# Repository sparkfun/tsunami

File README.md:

_Note: This repository is for the Tsunami Super WAV Trigger v1.1. For v1.2, check out the [Tsunami Super WAV Trigger (Qwiic) v1.2 GitHub repository](https://github.com/sparkfun/SparkFun_Tsunami_Super_WAV_Trigger_Qwiic)._

Tsunami Super WAV Trigger
========================================

[*Tsunami Super WAV Trigger (WIG-13810)*](https://www.sparkfun.com/products/retired/13810)

Tsunami is a polyphonic Wav file player with 4 stereo (or 8 mono) outputs.  Wav files can be triggered using the 16 onboard contacts, via MIDI, or using a serial connection to a PC or other microcontroller.

Repository Contents
-------------------

* **/Documentation** - Data sheets, additional product information
* **/Hardware** - Eagle design files (.brd, .sch)
* **/Production** - Production panel files (.brd)

Documentation
--------------
* **[Hookup Guide](https://learn.sparkfun.com/tutorials/tsunami-hookup-guide)** - Basic hookup guide for Tsunami v1.1.
* **[Official User Guide](https://cdn.sparkfun.com/assets/e/9/9/8/e/Tsunami_UserGuide_20230114.pdf)** - More detailed user guide, hosted by Robertsonics.
* **[Official Downloads Page](http://robertsonics.com/downloads/)** - Download supporting files, including firmware updates and the configuration utility.
* **[SparkFun Fritzing repo](https://github.com/sparkfun/Fritzing_Parts)** - Fritzing diagrams for SparkFun products.
* **[SparkFun 3D Model repo](https://github.com/sparkfun/3D_Models)** - 3D models of SparkFun products.

Product Versions
----------------
* [WIG-13810](https://www.sparkfun.com/products/13810) - First hardware revision.

Version History
---------------
* [Initial production Release](https://github.com/sparkfun/tsunami/commit/f42b14d72773535e83374cde73f2ca3f25164abb) - V11 hardware revision.

License Information
-------------------

The hardware design of Tsunami is _**open source**_!

Please review the LICENSE.md file for license information.

If you have any questions or concerns on licensing, please contact techsupport@sparkfun.com.

Distributed as-is; no warranty is given.

- Your friends at SparkFun.

Authors
----

Jamie Robertson @ Robertsonics & Byron Jacquot @ SparkFun Electronics

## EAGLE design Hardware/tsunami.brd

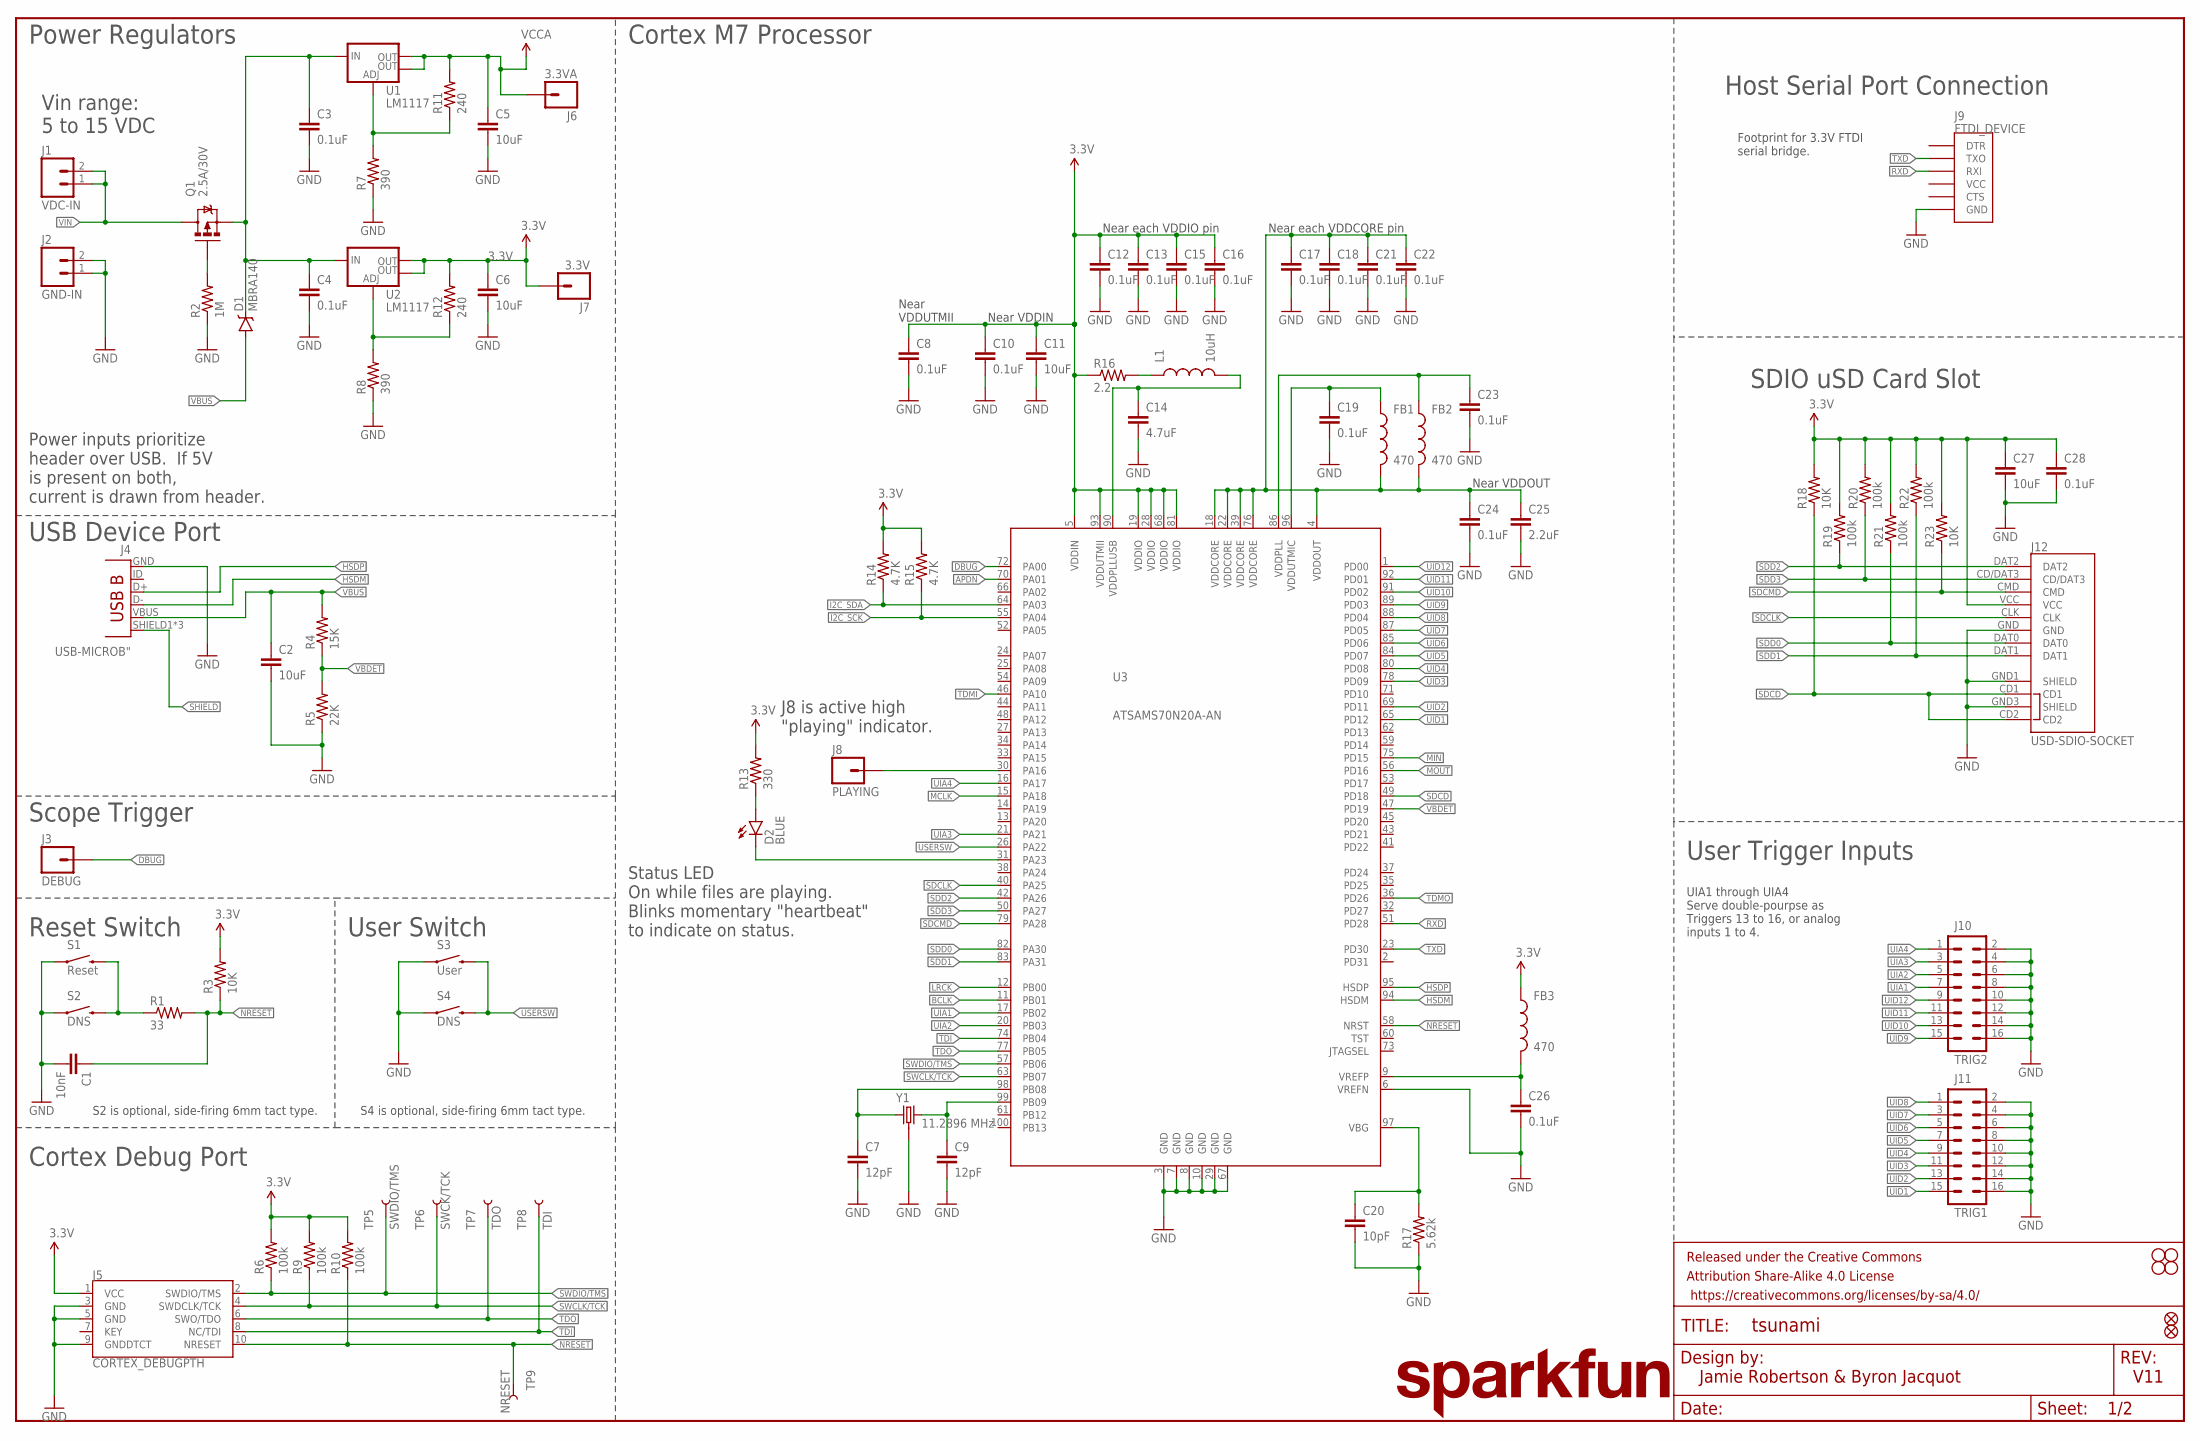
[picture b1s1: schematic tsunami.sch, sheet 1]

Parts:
C1: 10nF; 0603-CAP
C2, C5, C6, C11, C27: 10uF; 0603-CAP
C3, C4, C8, C10, C12, C13, C15, C16, C17, C18, C19, C21, C22, C23, C24, C26, C28: 0.1uF; 0603-CAP
C7, C9: 12pF; 0603-CAP
C14: 4.7uF; 0603-CAP
C20: 10pF; 0603-CAP
C25: 2.2uF; 0603-CAP
D1: MBRA140; SMA-DIODE
D2: BLUE; LED-0603
FB1, FB2, FB3: 470; 0603
FD1, FD2: FIDUCIALUFIDUCIAL; MICRO-FIDUCIAL
FRAME1: FRAME-LEDGER; CREATIVE_COMMONS
H1, H2, H3, H4: STAND-OFF
J1: VDC-IN; 1X02
J2: GND-IN; 1X02
J3: DEBUG; 1X01_NO_SILK
J4: USB-MICROB"; USB-B-MICRO-SMD_V03
J5: CORTEX_DEBUGPTH; 2X5-PTH-1.27MM
J6: 3.3VA; 1X01_NO_SILK
J7: 3.3V; 1X01_NO_SILK
J8: PLAYING; 1X01_NO_SILK
J9: FTDI_DEVICE; FTDI_DEVICE_SIDE
J10: TRIG2; 2X8
J11: TRIG1; 2X8
J12: USD-SDIO-SOCKET; MICRO-SD-SOCKET-SDIO
L1: 10uH; 0805
LOGO1: SFE_LOGO_NAME.2_INCH; SFE_LOGO_NAME_.2
Q1: 2.5A/30V; SOT23-3
R1: 33; 0603-RES
R2: 1M; 0603-RES
R3, R18, R23: 10K; 0603-RES
R4: 15K; 0603-RES
R5: 22K; 0603-RES
R6, R9, R10, R19, R20, R21, R22: 100k; 0603-RES
R7, R8: 390; 0603-RES
R11, R12: 240; 0603-RES
R13: 330; 0603-RES
R14, R15: 4.7K; 0603-RES
R16: 2.2; 0603-RES
R17: 5.62k; 0603-RES
S1: Reset; TACTILE-SWITCH-SMD
S2, S4: DNS; TACTILE-PTH-SIDEEZ
S3: User; TACTILE-SWITCH-SMD
TP5: SWDIO/TMS; TP_15TH
TP6: SWCK/TCK; TP_15TH
TP7: TDO; TP_15TH
TP8: TDI; TP_15TH
TP9: NRESET; TP_15TH
U1, U2: LM1117; SOT223
U3: ATSAMS70N20A-AN; LQFP100
Y1: 11.2896 MHz; CRYSTAL-OSC-SMD-5X3

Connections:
3.3V: C6.1, C8.1, C10.1, C11.1, C12.1, C13.1, C15.1, C16.1, C27.1, C28.1, FB3.1, J5.1 (VCC), J7.1, J12.VCC, R3.2, R6.2, R9.2, R10.2, R12.2, R13.2, R14.2, R15.2, R16.1, R18.2, R19.2, R20.2, R21.2, R22.2, R23.2, U2.2 (OUT), U2.4 (OUT), U3.5 (VDDIN), U3.19 (VDDIO), U3.28 (VDDIO), U3.68 (VDDIO), U3.81 (VDDIO), U3.93 (VDDUTMII); also elsewhere on the board
APDN: U3.70 (PA01); also elsewhere on the board
BCLK: U3.11 (PB01); also elsewhere on the board
DBUG: J3.1, U3.72 (PA00)
GND: C1.2, C2.2, C3.2, C4.2, C5.2, C6.2, C7.2, C8.2, C9.2, C10.2, C11.2, C12.2, C13.2, C14.2, C15.2, C16.2, C17.2, C18.2, C19.2, C20.2, C21.2, C22.2, C23.2, C24.2, C25.2, C26.2, C27.2, C28.2, J2.1, J2.2, J4.GND, J5.3 (GND), J5.5 (GND), J5.9 (GNDDTCT), J9.P$6 (GND), J10.2, J10.4, J10.6, J10.8, J10.10, J10.12, J10.14, J10.16, J11.2, J11.4, J11.6, J11.8, J11.10, J11.12, J11.14, J11.16, J12.GND, J12.GND1 (SHIELD), J12.GND3 (SHIELD), R2.1, R5.1, R7.1, R8.1, R17.1, S1.1, S2.1, S3.1, S4.1, U3.3 (GND), U3.6 (VREFN), U3.7 (GND), U3.8 (GND), U3.10 (GND), U3.29 (GND), U3.67 (GND), Y1.2 (3), Y1.4 (3); also elsewhere on the board
HSDM: J4.D-, U3.94 (HSDM)
HSDP: J4.D+, U3.95 (HSDP)
I2C_SCK: R15.1, U3.55 (PA04); also elsewhere on the board
I2C_SDA: R14.1, U3.64 (PA03); also elsewhere on the board
LRCK: U3.12 (PB00); also elsewhere on the board
MCLK: U3.15 (PA18); also elsewhere on the board
MIN: U3.75 (PD15); also elsewhere on the board
MOUT: U3.56 (PD16); also elsewhere on the board
unnamed: C7.1, U3.98 (PB08), Y1.1
unnamed: C9.1, U3.99 (PB09), Y1.3 (2)
unnamed: C19.1, FB1.1, U3.96 (VDDUTMIC)
unnamed: C14.1, L1.2, U3.90 (VDDPLLUSB)
unnamed: C23.1, FB2.1, U3.86 (VDDPLL)
unnamed: J8.1, U3.30 (PA16)
unnamed: D2.C, U3.31 (PA23)
unnamed: D2.A, R13.1
unnamed: C20.1, R17.2, U3.97 (VBG)
unnamed: C26.1, FB3.2, U3.9 (VREFP)
unnamed: L1.1, R16.2
unnamed: R7.2, R11.1, U1.1 (ADJ)
unnamed: R1.1, S1.3 (2), S2.2
unnamed: R8.2, R12.1, U2.1 (ADJ)
unnamed: Q1.1 (G), R2.2
NRESET: C1.1, J5.10 (NRESET), R1.2, R3.1, R10.1, TP9.P$1, U3.58 (NRST)
REGINPUTS: C3.1, C4.1, D1.C, Q1.2 (S), U1.3 (IN), U2.3 (IN)
RXD: J9.P$3 (RXI), U3.51 (PD28)
SDCD: J12.CD1, J12.CD2, R18.1, U3.49 (PD18)
SDCLK: J12.CLK, U3.40 (PA25)
SDCMD: J12.CMD, R23.1, U3.79 (PA28)
SDD0: J12.DAT0, R21.1, U3.82 (PA30)
SDD1: J12.DAT1, R22.1, U3.83 (PA31)
SDD2: J12.DAT2, R19.1, U3.42 (PA26)
SDD3: J12.CD/DAT3, R20.1, U3.50 (PA27)
SHIELD: J4.SHIELD1 (SHIELD), J4.SHIELD2 (SHIELD), J4.SHIELD3 (SHIELD)
SWCLK/TCK: J5.4 (SWDCLK/TCK), R9.1, TP6.P$1, U3.63 (PB07)
SWDIO/TMS: J5.2 (SWDIO/TMS), R6.1, TP5.P$1, U3.57 (PB06)
TDI: J5.8 (NC/TDI), TP8.P$1, U3.74 (PB04)
TDMI: U3.46 (PA10); also elsewhere on the board
TDMO: U3.36 (PD26); also elsewhere on the board
TDO: J5.6 (SWO/TDO), TP7.P$1, U3.77 (PB05)
TXD: J9.P$2 (TXO), U3.23 (PD30)
UIA1: J10.7, U3.17 (PB02)
UIA2: J10.5, U3.20 (PB03)
UIA3: J10.3, U3.21 (PA21)
UIA4: J10.1, U3.16 (PA17)
UID1: J11.15, U3.65 (PD12)
UID2: J11.13, U3.69 (PD11)
UID3: J11.11, U3.78 (PD09)
UID4: J11.9, U3.80 (PD08)
UID5: J11.7, U3.84 (PD07)
UID6: J11.5, U3.85 (PD06)
UID7: J11.3, U3.87 (PD05)
UID8: J11.1, U3.88 (PD04)
UID9: J10.15, U3.89 (PD03)
UID10: J10.13, U3.91 (PD02)
UID11: J10.11, U3.92 (PD01)
UID12: J10.9, U3.1 (PD00)
USERSW: S3.3 (2), S4.2, U3.26 (PA22)
VBDET: R4.1, R5.2, U3.47 (PD19)
VBUS: C2.1, D1.A, J4.VBUS, R4.2
VCCA: C5.1, J6.1, R11.2, U1.2 (OUT), U1.4 (OUT); also elsewhere on the board
VDDOUT: C17.1, C18.1, C21.1, C22.1, C24.1, C25.1, FB1.2, FB2.2, U3.4 (VDDOUT), U3.18 (VDDCORE), U3.22 (VDDCORE), U3.39 (VDDCORE), U3.76 (VDDCORE)
VIN: J1.1, J1.2, Q1.3 (D)

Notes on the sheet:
Jamie Robertson & Byron Jacquot
V11
Near each VDDCORE pin
Near each VDDIO pin
Near VDDUTMII
Near VDDIN
Near VDDOUT
Power Regulators
USB Device Port
Scope Trigger
Cortex Debug Port
Cortex M7 Processor
SDIO uSD Card Slot
User Trigger Inputs
Reset Switch
S2 is optional, side-firing 6mm tact type.
Vin range: 5 to 15 VDC
Status LED On while files are playing. Blinks momentary "heartbeat" to indicate on status.
Power inputs prioritize header over USB. If 5V is present on both, current is drawn from header.
UIA1 through UIA4 Serve double-pourpse as Triggers 13 to 16, or analog inputs 1 to 4.
Host Serial Port Connection
Footprint for 3.3V FTDI serial bridge.
User Switch
J8 is active high "playing" indicator.
S4 is optional, side-firing 6mm tact type.

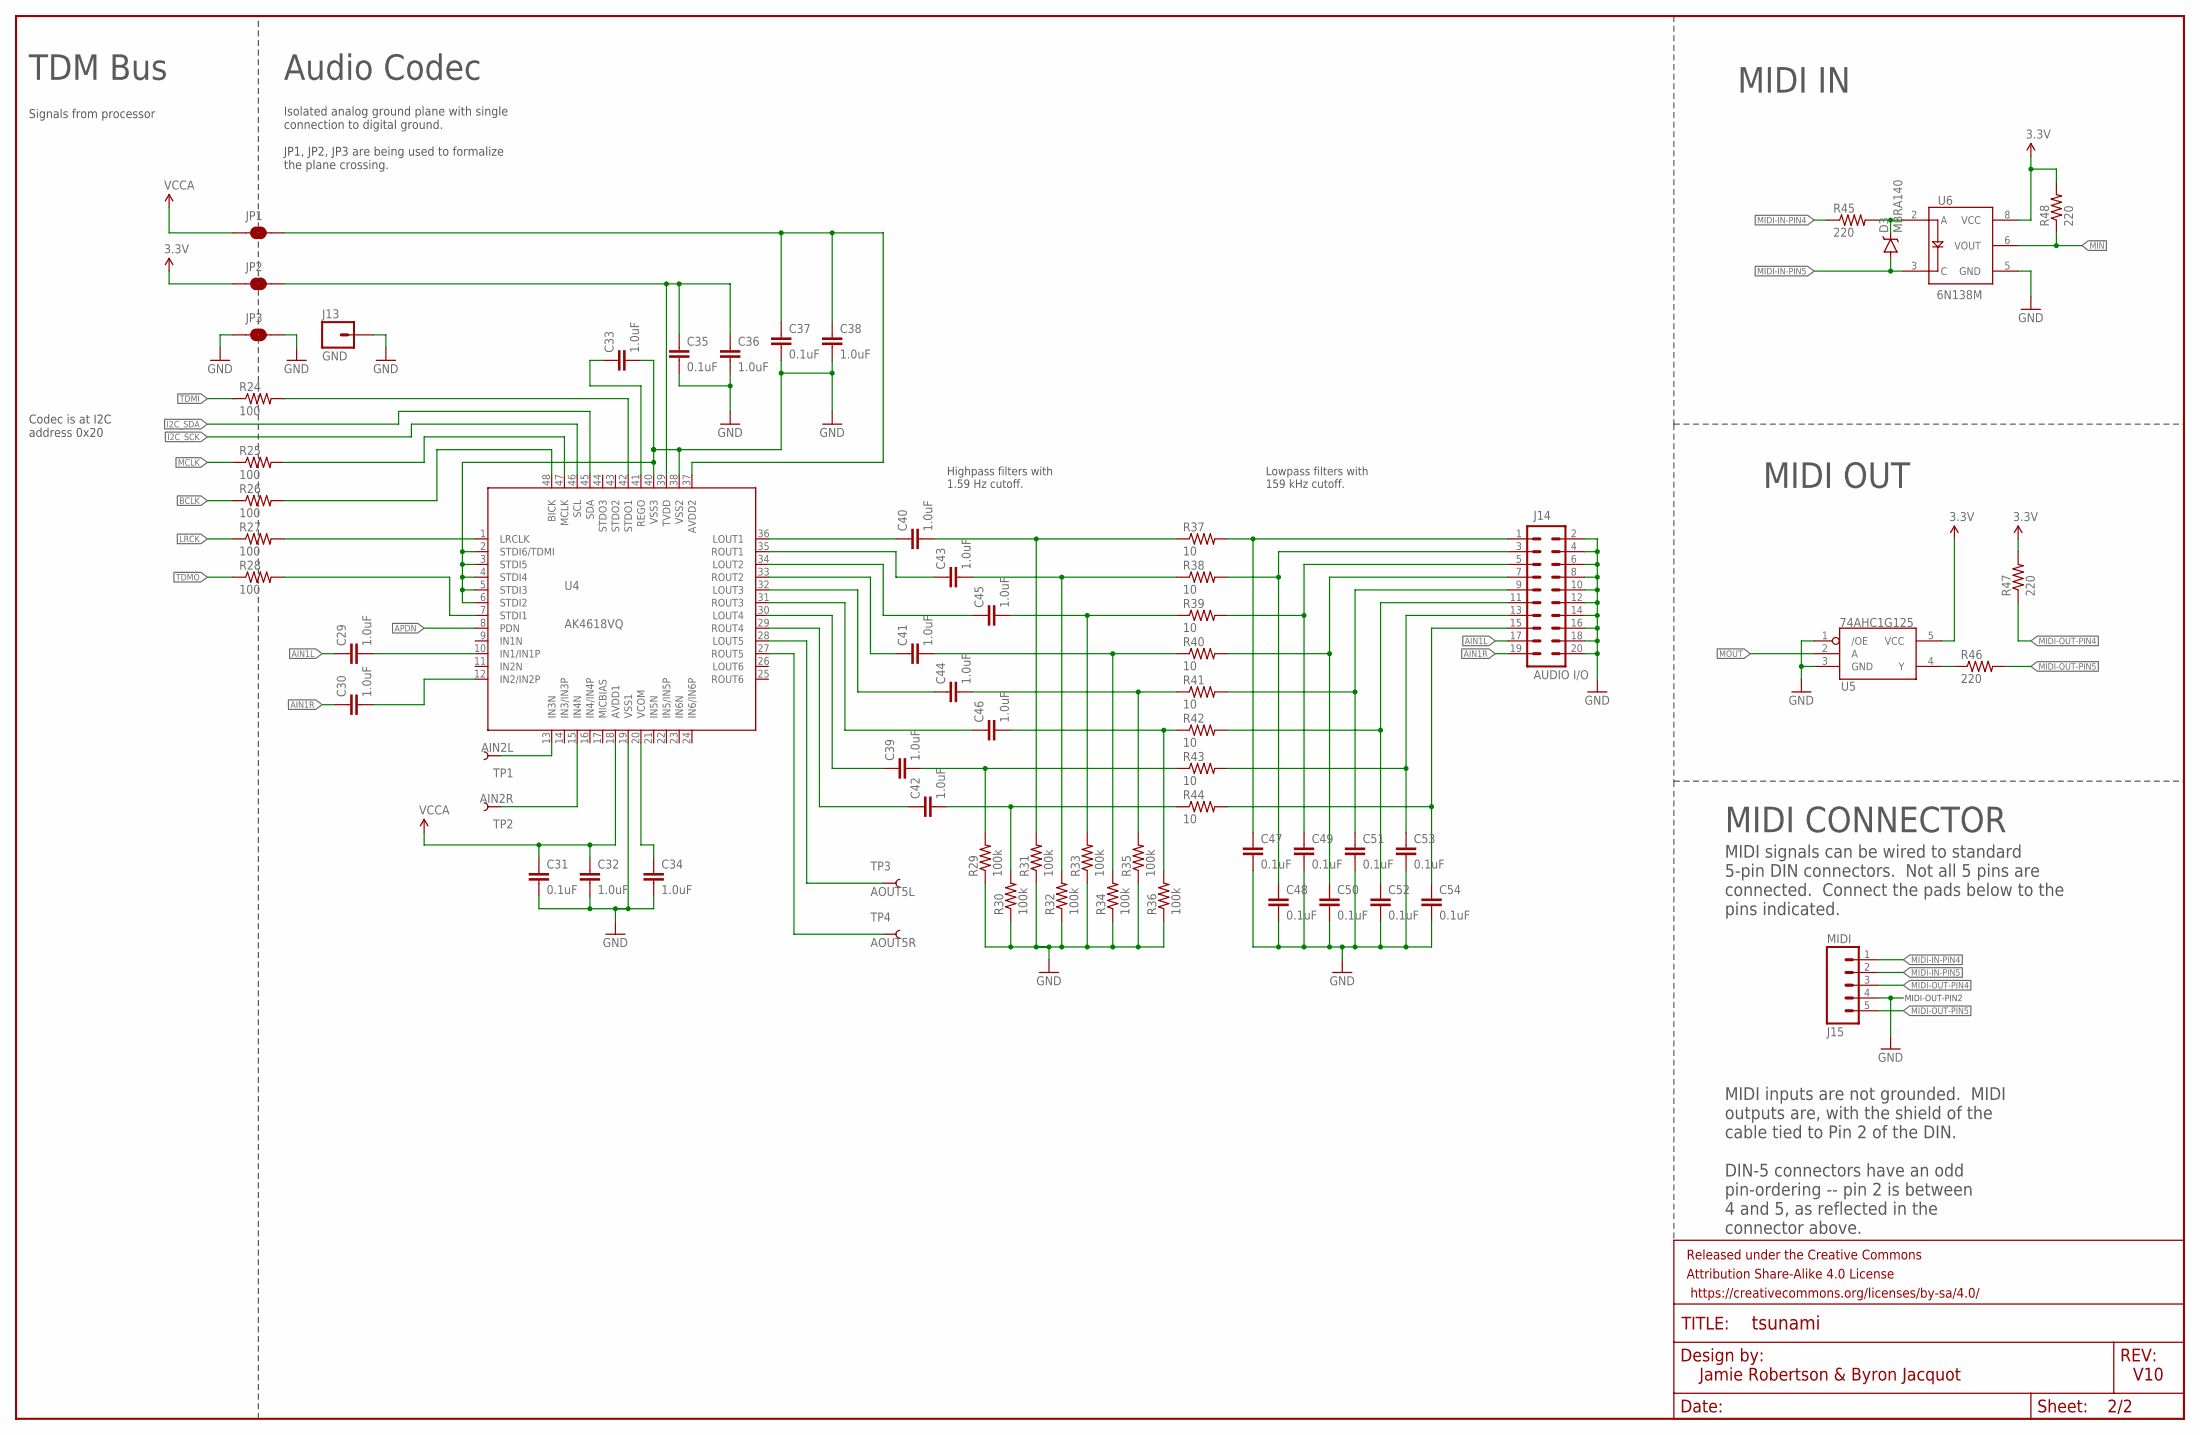
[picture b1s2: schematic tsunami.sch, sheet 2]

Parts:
C29, C30, C32, C33, C34, C36, C38, C39, C40, C41, C42, C43, C44, C45, C46: 1.0uF; 0603-CAP
C31, C35, C37, C47, C48, C49, C50, C51, C52, C53, C54: 0.1uF; 0603-CAP
D3: MBRA140; SMA-DIODE
FRAME2: FRAME-LEDGER; CREATIVE_COMMONS
J13: GND; 1X01_NO_SILK
J14: AUDIO I/O; 2X10
J15: MIDI; 1X05_NO_SILK
JP1, JP2, JP3: JUMPER-PAD-2-NC_BY_TRACENO_SILK; PAD-JUMPER-2-NC_BY_TRACE_NO_SILK
R24, R25, R26, R27, R28: 100; 0603-RES
R29, R30, R31, R32, R33, R34, R35, R36: 100k; 0603-RES
R37, R38, R39, R40, R41, R42, R43, R44: 10; 0603-RES
R45, R46, R47, R48: 220; 0603-RES
TP1: AIN2L; TP_15TH
TP2: AIN2R; TP_15TH
TP3: AOUT5L; TP_15TH
TP4: AOUT5R; TP_15TH
U4: AK4618VQ; LQFP-48
U5: 74AHC1G125; SOT23-5
U6: 6N138M; 8-SMD

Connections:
3.3V: C35.1, C36.1, JP2.1, JP2.2, R47.2, R48.2, U4.39 (TVDD), U5.5 (VCC), U6.8 (VCC); also elsewhere on the board
56: D3.C, R45.2, U6.2 (A)
AIN1L: C29.1, J14.17
AIN1R: C30.1, J14.19
AIN2L: TP1.P$1, U4.13 (IN3N)
AIN2R: TP2.P$1, U4.15 (IN4N)
AOUT1L: C47.1, J14.1, R37.2
AOUT1R: C48.1, J14.3, R38.2
AOUT2L: C49.1, J14.5, R39.2
AOUT2R: C50.1, J14.7, R40.2
AOUT3L: C51.1, J14.9, R41.2
AOUT3R: C52.1, J14.11, R42.2
AOUT4L: C53.1, J14.13, R43.2
AOUT4R: C54.1, J14.15, R44.2
APDN: U4.8 (PDN); also elsewhere on the board
BCLK: R26.1; also elsewhere on the board
BCLK_C: R26.2, U4.48 (BICK)
GND: C31.2, C32.2, C33.2, C34.2, C35.2, C36.2, C37.2, C38.2, C47.2, C48.2, C49.2, C50.2, C51.2, C52.2, C53.2, C54.2, J13.1, J14.2, J14.4, J14.6, J14.8, J14.10, J14.12, J14.14, J14.16, J14.18, J14.20, J15.4, JP3.1, JP3.2, R29.1, R30.1, R31.1, R32.1, R33.1, R34.1, R35.1, R36.1, U4.2 (STDI6/TDMI), U4.3 (STDI5), U4.4 (STDI4), U4.5 (STDI3), U4.6 (STDI2), U4.19 (VSS1), U4.38 (VSS2), U4.40 (VSS3), U5.1 (/OE), U5.3 (GND), U6.5 (GND); also elsewhere on the board
I2C_SCK: U4.46 (SCL); also elsewhere on the board
I2C_SDA: U4.45 (SDA); also elsewhere on the board
LRCK: R27.1; also elsewhere on the board
LRCK_C: R27.2, U4.1 (LRCLK)
MCLK: R25.1; also elsewhere on the board
MCLK_C: R25.2, U4.47 (MCLK)
MIDI-IN-PIN4: J15.1, R45.1
MIDI-IN-PIN5: D3.A, J15.2, U6.3 (C)
MIDI-OUT-PIN4: J15.3, R47.1
MIDI-OUT-PIN5: J15.5, R46.2
MIN: R48.1, U6.6 (VOUT); also elsewhere on the board
MOUT: U5.2 (A); also elsewhere on the board
unnamed: C33.1, U4.41 (REGO)
unnamed: C34.1, U4.20 (VCOM)
unnamed: C40.1, U4.36 (LOUT1)
unnamed: C30.2, U4.12 (IN2/IN2P)
unnamed: C29.2, U4.10 (IN1/IN1P)
unnamed: C43.1, U4.35 (ROUT1)
unnamed: C45.1, U4.34 (LOUT2)
unnamed: C41.1, U4.33 (ROUT2)
unnamed: C44.1, U4.32 (LOUT3)
unnamed: C46.1, U4.31 (ROUT3)
unnamed: C40.2, R31.2, R37.1
unnamed: C42.2, R30.2, R44.1
unnamed: C39.2, R29.2, R43.1
unnamed: C46.2, R36.2, R42.1
unnamed: C39.1, U4.30 (LOUT4)
unnamed: C42.1, U4.29 (ROUT4)
unnamed: TP3.P$1, U4.28 (LOUT5)
unnamed: TP4.P$1, U4.27 (ROUT5)
unnamed: R46.1, U5.4 (Y)
unnamed: C44.2, R35.2, R41.1
unnamed: C41.2, R34.2, R40.1
unnamed: C43.2, R32.2, R38.1
unnamed: C45.2, R33.2, R39.1
TDMI: R24.1; also elsewhere on the board
TDMI_C: R24.2, U4.42 (STDO1)
TDMO: R28.1; also elsewhere on the board
TDMO_C: R28.2, U4.7 (STDI1)
VCCA: C31.1, C32.1, C37.1, C38.1, JP1.1, JP1.2, U4.18 (AVDD1), U4.37 (AVDD2); also elsewhere on the board

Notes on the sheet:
Isolated analog ground plane with single connection to digital ground. JP1, JP2, JP3 are being used to formalize the plane crossing.
Audio Codec
MIDI IN
MIDI OUT
Jamie Robertson & Byron Jacquot
V10
TDM Bus
Signals from processor
MIDI CONNECTOR
MIDI signals can be wired to standard 5-pin DIN connectors. Not all 5 pins are connected. Connect the pads below to the pins indicated.
MIDI-OUT-PIN2
Codec is at I2C address 0x20
MIDI inputs are not grounded. MIDI outputs are, with the shield of the cable tied to Pin 2 of the DIN. DIN-5 connectors have an odd pin-ordering -- pin 2 is between 4 and 5, as reflected in the connector above.
Highpass filters with 1.59 Hz cutoff.
Lowpass filters with 159 kHz cutoff.

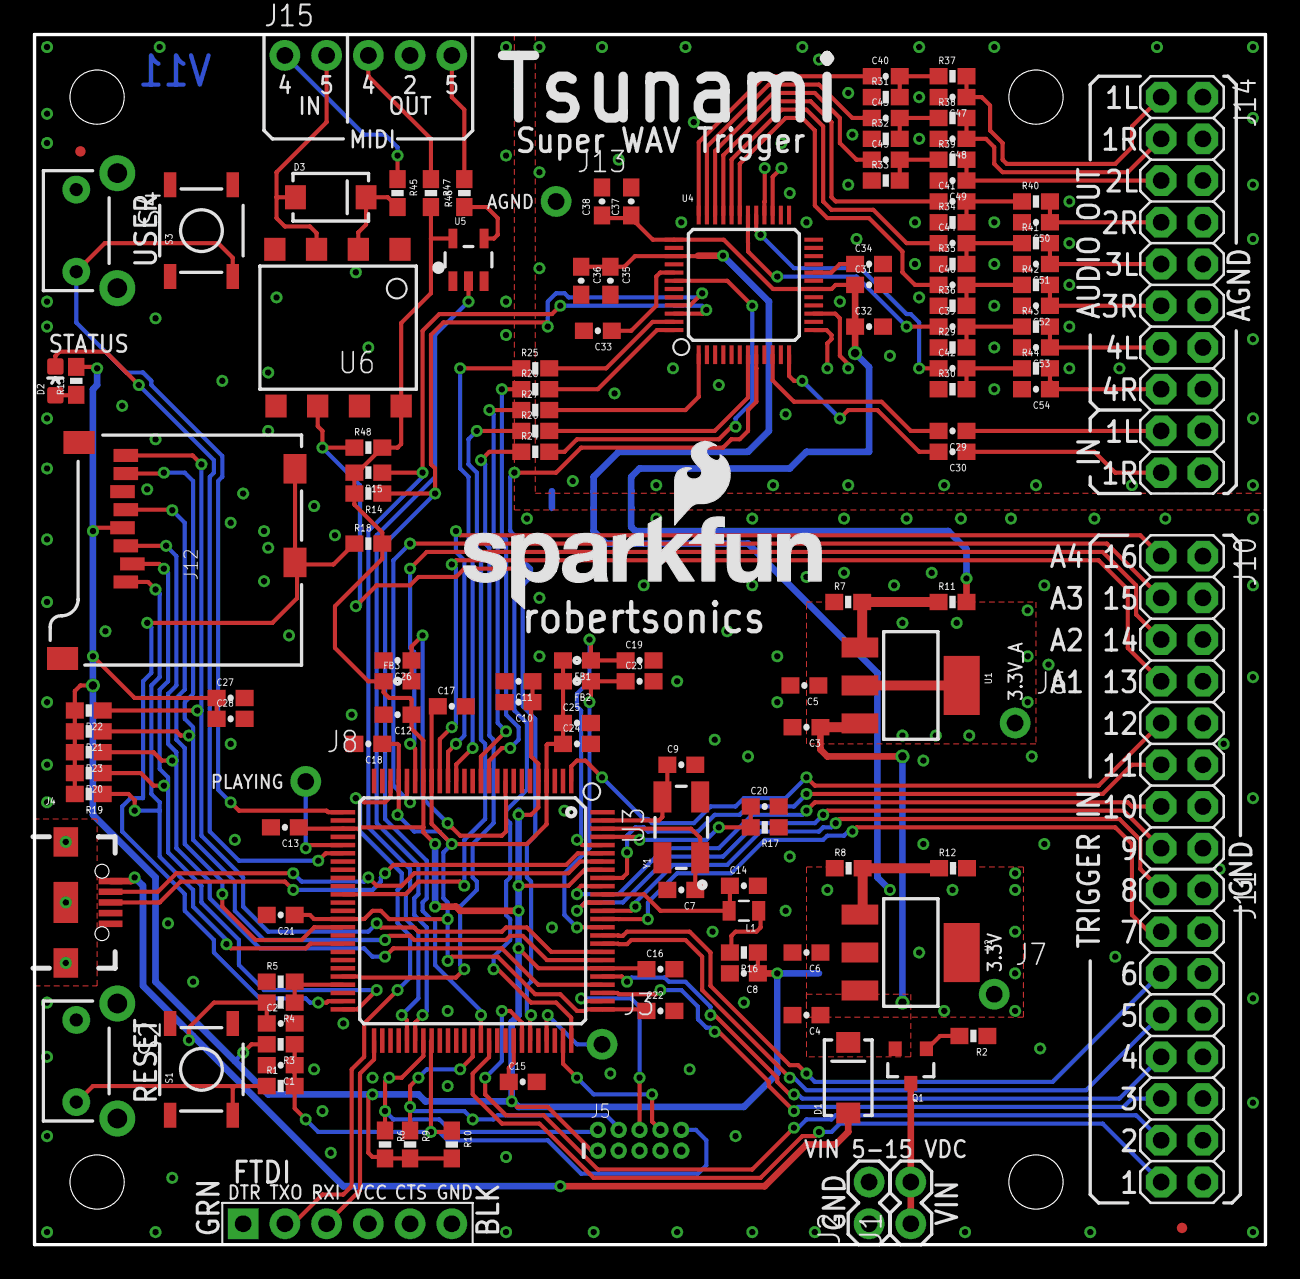
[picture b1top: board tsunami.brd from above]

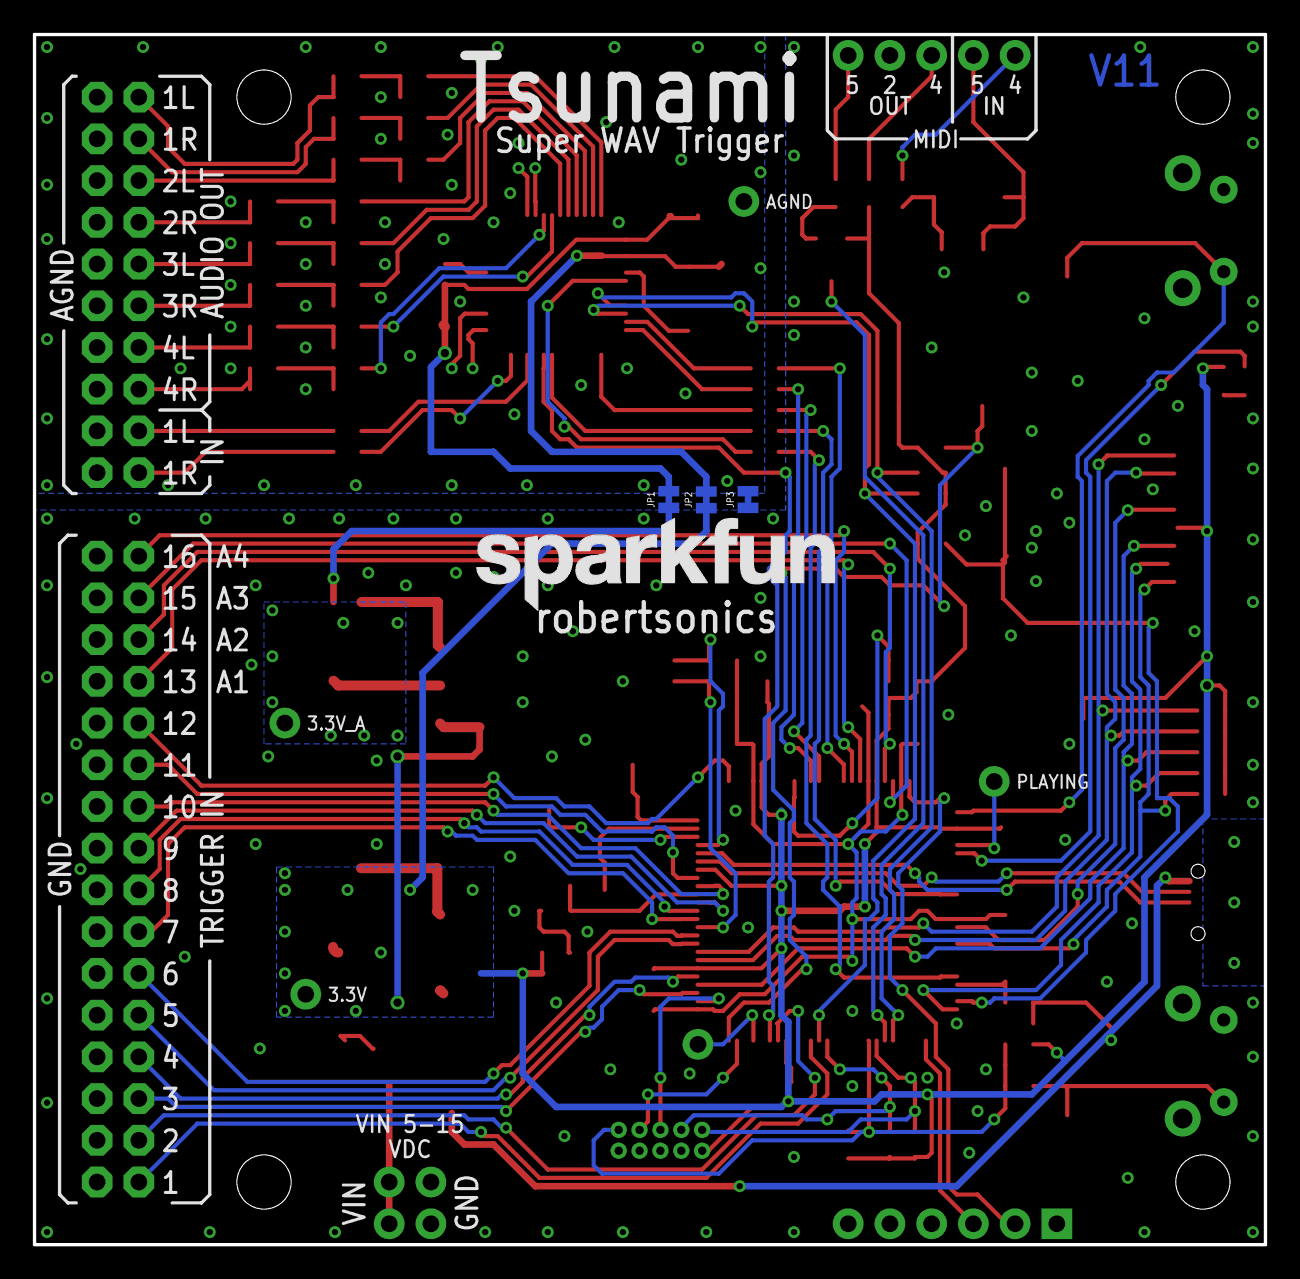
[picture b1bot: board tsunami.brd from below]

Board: 2 copper layers, 74.9 x 73.7 mm, 158 parts (4 on the bottom side), 113 nets.

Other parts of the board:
LOGO4: SFE_LOGO_NAME_FLAME.2_INCH; SFE_LOGO_NAME_FLAME_.2

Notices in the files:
parts and their libraries:
SparkFun-Aesthetics: Licensing: Creative Commons ShareAlike 4.0 International - https://creativecommons.org/licenses/by-sa/4.0
SparkFun-Aesthetics: Released under the Creative Commons Attribution Share-Alike 4.0 License
SparkFun-Aesthetics: https://creativecommons.org/licenses/by-sa/4.0
